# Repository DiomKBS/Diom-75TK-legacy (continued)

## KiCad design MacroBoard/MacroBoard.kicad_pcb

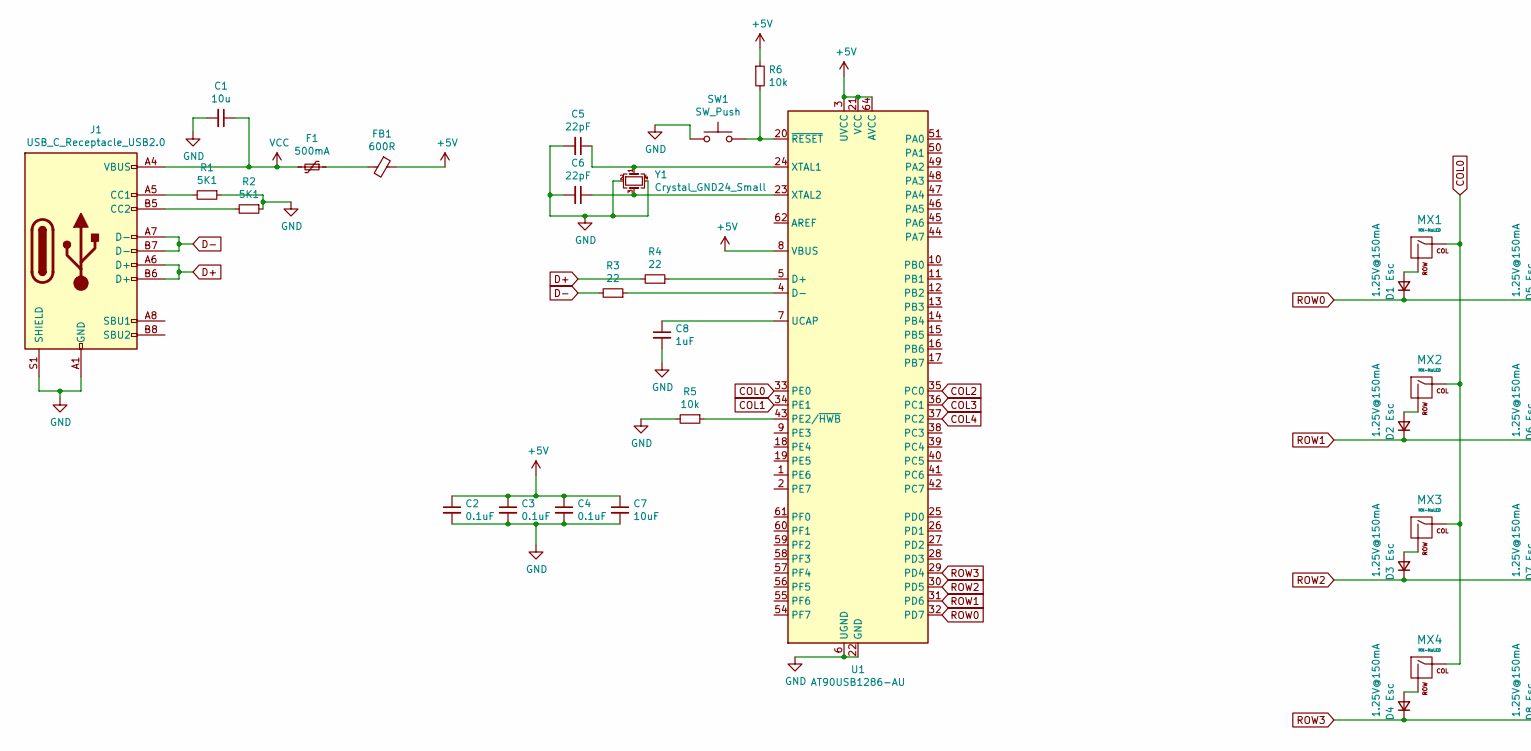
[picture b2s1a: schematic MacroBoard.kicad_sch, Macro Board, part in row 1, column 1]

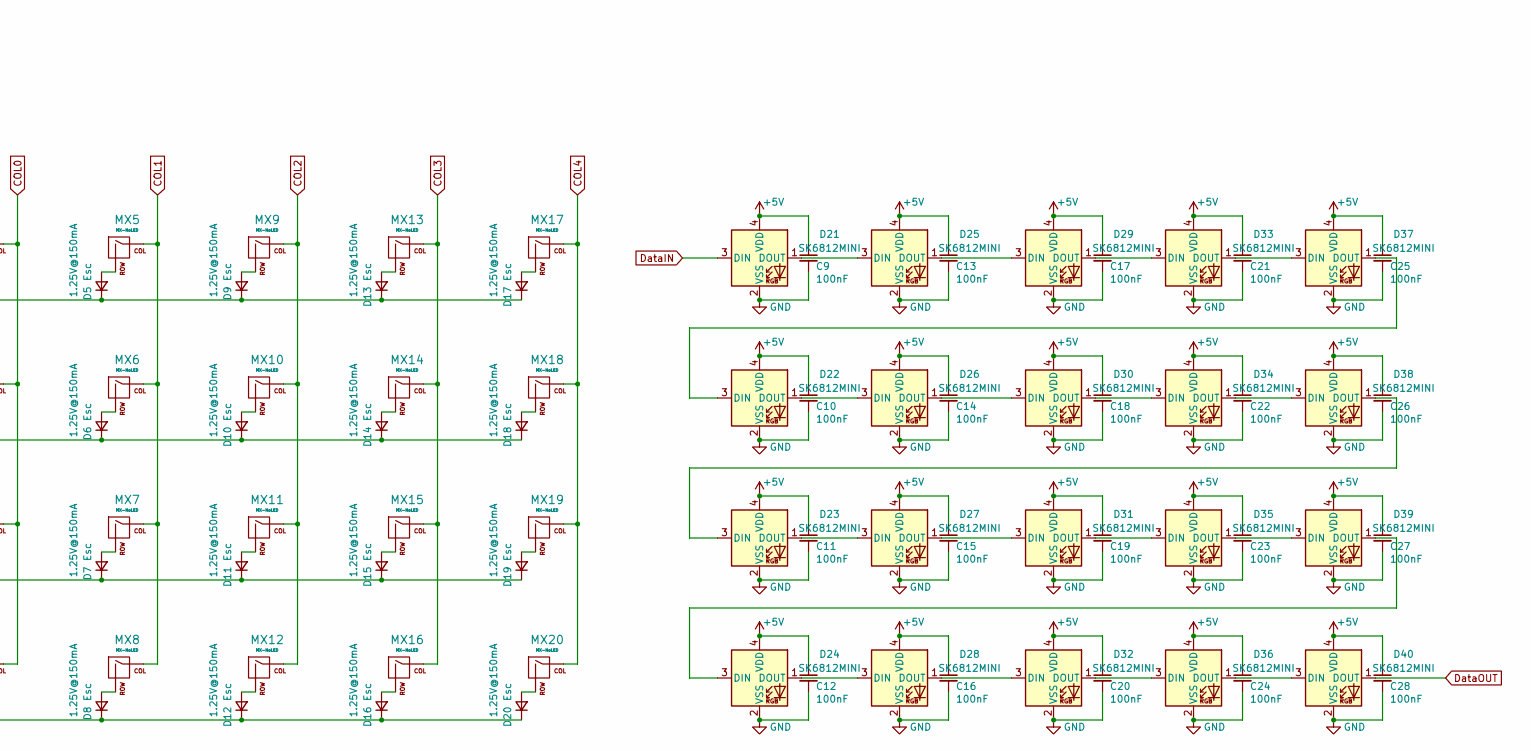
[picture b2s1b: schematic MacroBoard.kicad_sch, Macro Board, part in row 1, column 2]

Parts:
C1: 10u; C_0805_2012Metric
C2, C3, C4: 0.1uF; C_0805_2012Metric
C5, C6: 22pF; C_0805_2012Metric
C7: 10uF; C_0805_2012Metric
C8: 1uF; C_0805_2012Metric
C9, C10, C11, C12, C13, C14, C15, C16, C17, C18, C19, C20, C21, C22, C23, C24, C25, C26, C27, C28: 100nF; led_capacitor
D1, D2, D3, D4, D5, D6, D7, D8, D9, D10, D11, D12, D13, D14, D15, D16, D17, D18, D19, D20: 1.25V@150mA; D_SOD-123
D21, D22, D23, D24, D25, D26, D27, D28, D29, D30, D31, D32, D33, D34, D35, D36, D37, D38, D39, D40: SK6812MINI; SK6812MINI_3.5x3.7mm_SMD-Flipped-Back
F1: 500mA; Fuse_1206_3216Metric
FB1: 600R; Ferrite_Bead_0603
J1: USB_C_Receptacle_USB2.0; USB_C_Receptacle_HRO_TYPE-C-31-M-12
MX1, MX2, MX3, MX4, MX5, MX6, MX7, MX8, MX9, MX10, MX11, MX12, MX13, MX14, MX15, MX16, MX17, MX18, MX19, MX20: MX-NoLED; Kailh-Hotswap-1U
R1, R2: 5K1; R_0805_2012Metric
R3, R4: 22; R_0805_2012Metric
R5, R6: 10k; R_0805_2012Metric
SW1: SW_Push; SKQG-1155865
U1: AT90USB1286-AU; TQFP-64_14x14mm_P0.8mm
Y1: Crystal_GND24_Small; Crystal_SMD_3225-4Pin_3.2x2.5mm

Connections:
+5V: C2.1, C3.1, C4.1, C7.1, C9.1, C10.1, C11.1, C12.1, C13.1, C14.1, C15.1, C16.1, C17.1, C18.1, C19.1, C20.1, C21.1, C22.1, C23.1, C24.1, C25.1, C26.1, C27.1, C28.1, D21.4 (VDD), D22.4 (VDD), D23.4 (VDD), D24.4 (VDD), D25.4 (VDD), D26.4 (VDD), D27.4 (VDD), D28.4 (VDD), D29.4 (VDD), D30.4 (VDD), D31.4 (VDD), D32.4 (VDD), D33.4 (VDD), D34.4 (VDD), D35.4 (VDD), D36.4 (VDD), D37.4 (VDD), D38.4 (VDD), D39.4 (VDD), D40.4 (VDD), FB1.1, R6.1, U1.3 (UVCC), U1.8 (VBUS), U1.21 (VCC), U1.52 (VCC), U1.64 (AVCC)
COL0: MX1.1 (COL), MX2.1 (COL), MX3.1 (COL), MX4.1 (COL), U1.33 (PE0)
COL1: MX5.1 (COL), MX6.1 (COL), MX7.1 (COL), MX8.1 (COL), U1.34 (PE1)
COL2: MX9.1 (COL), MX10.1 (COL), MX11.1 (COL), MX12.1 (COL), U1.35 (PC0)
COL3: MX13.1 (COL), MX14.1 (COL), MX15.1 (COL), MX16.1 (COL), U1.36 (PC1)
COL4: MX17.1 (COL), MX18.1 (COL), MX19.1 (COL), MX20.1 (COL), U1.37 (PC2)
D+: J1.A6 (D+), J1.B6 (D+), R4.2
D-: J1.A7 (D-), J1.B7 (D-), R3.2
DataIN: D21.3 (DIN)
DataOUT: D40.1 (DOUT)
GND: C1.2, C2.2, C3.2, C4.2, C5.2, C6.2, C7.2, C8.2, C9.2, C10.2, C11.2, C12.2, C13.2, C14.2, C15.2, C16.2, C17.2, C18.2, C19.2, C20.2, C21.2, C22.2, C23.2, C24.2, C25.2, C26.2, C27.2, C28.2, D21.2 (VSS), D22.2 (VSS), D23.2 (VSS), D24.2 (VSS), D25.2 (VSS), D26.2 (VSS), D27.2 (VSS), D28.2 (VSS), D29.2 (VSS), D30.2 (VSS), D31.2 (VSS), D32.2 (VSS), D33.2 (VSS), D34.2 (VSS), D35.2 (VSS), D36.2 (VSS), D37.2 (VSS), D38.2 (VSS), D39.2 (VSS), D40.2 (VSS), J1.A1 (GND), J1.A12 (GND), J1.B1 (GND), J1.B12 (GND), J1.S1 (SHIELD), R1.1, R2.1, R5.2, SW1.1, U1.6 (UGND), U1.22 (GND), U1.53 (GND), U1.63 (GND), Y1.2, Y1.4
unnamed: C5.1, U1.24 (XTAL1), Y1.1
unnamed: C6.1, U1.23 (XTAL2), Y1.3
unnamed: C8.1, U1.7 (UCAP)
unnamed: D1.2 (A), MX1.2 (ROW)
unnamed: D2.2 (A), MX2.2 (ROW)
unnamed: D3.2 (A), MX3.2 (ROW)
unnamed: D4.2 (A), MX4.2 (ROW)
unnamed: D5.2 (A), MX5.2 (ROW)
unnamed: D6.2 (A), MX6.2 (ROW)
unnamed: D7.2 (A), MX7.2 (ROW)
unnamed: D8.2 (A), MX8.2 (ROW)
unnamed: D9.2 (A), MX9.2 (ROW)
unnamed: D10.2 (A), MX10.2 (ROW)
unnamed: D11.2 (A), MX11.2 (ROW)
unnamed: D12.2 (A), MX12.2 (ROW)
unnamed: D13.2 (A), MX13.2 (ROW)
unnamed: D14.2 (A), MX14.2 (ROW)
unnamed: D15.2 (A), MX15.2 (ROW)
unnamed: D16.2 (A), MX16.2 (ROW)
unnamed: D17.2 (A), MX17.2 (ROW)
unnamed: D18.2 (A), MX18.2 (ROW)
unnamed: D19.2 (A), MX19.2 (ROW)
unnamed: D20.2 (A), MX20.2 (ROW)
unnamed: D21.1 (DOUT), D25.3 (DIN)
unnamed: D22.1 (DOUT), D26.3 (DIN)
unnamed: D22.3 (DIN), D37.1 (DOUT)
unnamed: D23.1 (DOUT), D27.3 (DIN)
unnamed: D23.3 (DIN), D38.1 (DOUT)
unnamed: D24.1 (DOUT), D28.3 (DIN)
unnamed: D24.3 (DIN), D39.1 (DOUT)
unnamed: D25.1 (DOUT), D29.3 (DIN)
unnamed: D26.1 (DOUT), D30.3 (DIN)
unnamed: D27.1 (DOUT), D31.3 (DIN)
unnamed: D28.1 (DOUT), D32.3 (DIN)
unnamed: D29.1 (DOUT), D33.3 (DIN)
unnamed: D30.1 (DOUT), D34.3 (DIN)
unnamed: D31.1 (DOUT), D35.3 (DIN)
unnamed: D32.1 (DOUT), D36.3 (DIN)
unnamed: D33.1 (DOUT), D37.3 (DIN)
unnamed: D34.1 (DOUT), D38.3 (DIN)
unnamed: D35.1 (DOUT), D39.3 (DIN)
unnamed: D36.1 (DOUT), D40.3 (DIN)
unnamed: F1.1, FB1.2
unnamed: J1.A5 (CC1), R1.2
unnamed: J1.B5 (CC2), R2.2
unnamed: R3.1, U1.4 (D-)
unnamed: R4.1, U1.5 (D+)
unnamed: R5.1, U1.43 (PE2/~HWB)
unnamed: R6.2, SW1.2, U1.20 (~RESET)
ROW0: D1.1 (K), D5.1 (K), D9.1 (K), D13.1 (K), D17.1 (K), U1.32 (PD7)
ROW1: D2.1 (K), D6.1 (K), D10.1 (K), D14.1 (K), D18.1 (K), U1.31 (PD6)
ROW2: D3.1 (K), D7.1 (K), D11.1 (K), D15.1 (K), D19.1 (K), U1.30 (PD5)
ROW3: D4.1 (K), D8.1 (K), D12.1 (K), D16.1 (K), D20.1 (K), U1.29 (PD4)
VCC: C1.1, F1.2, J1.A4 (VBUS), J1.A9 (VBUS), J1.B4 (VBUS), J1.B9 (VBUS)

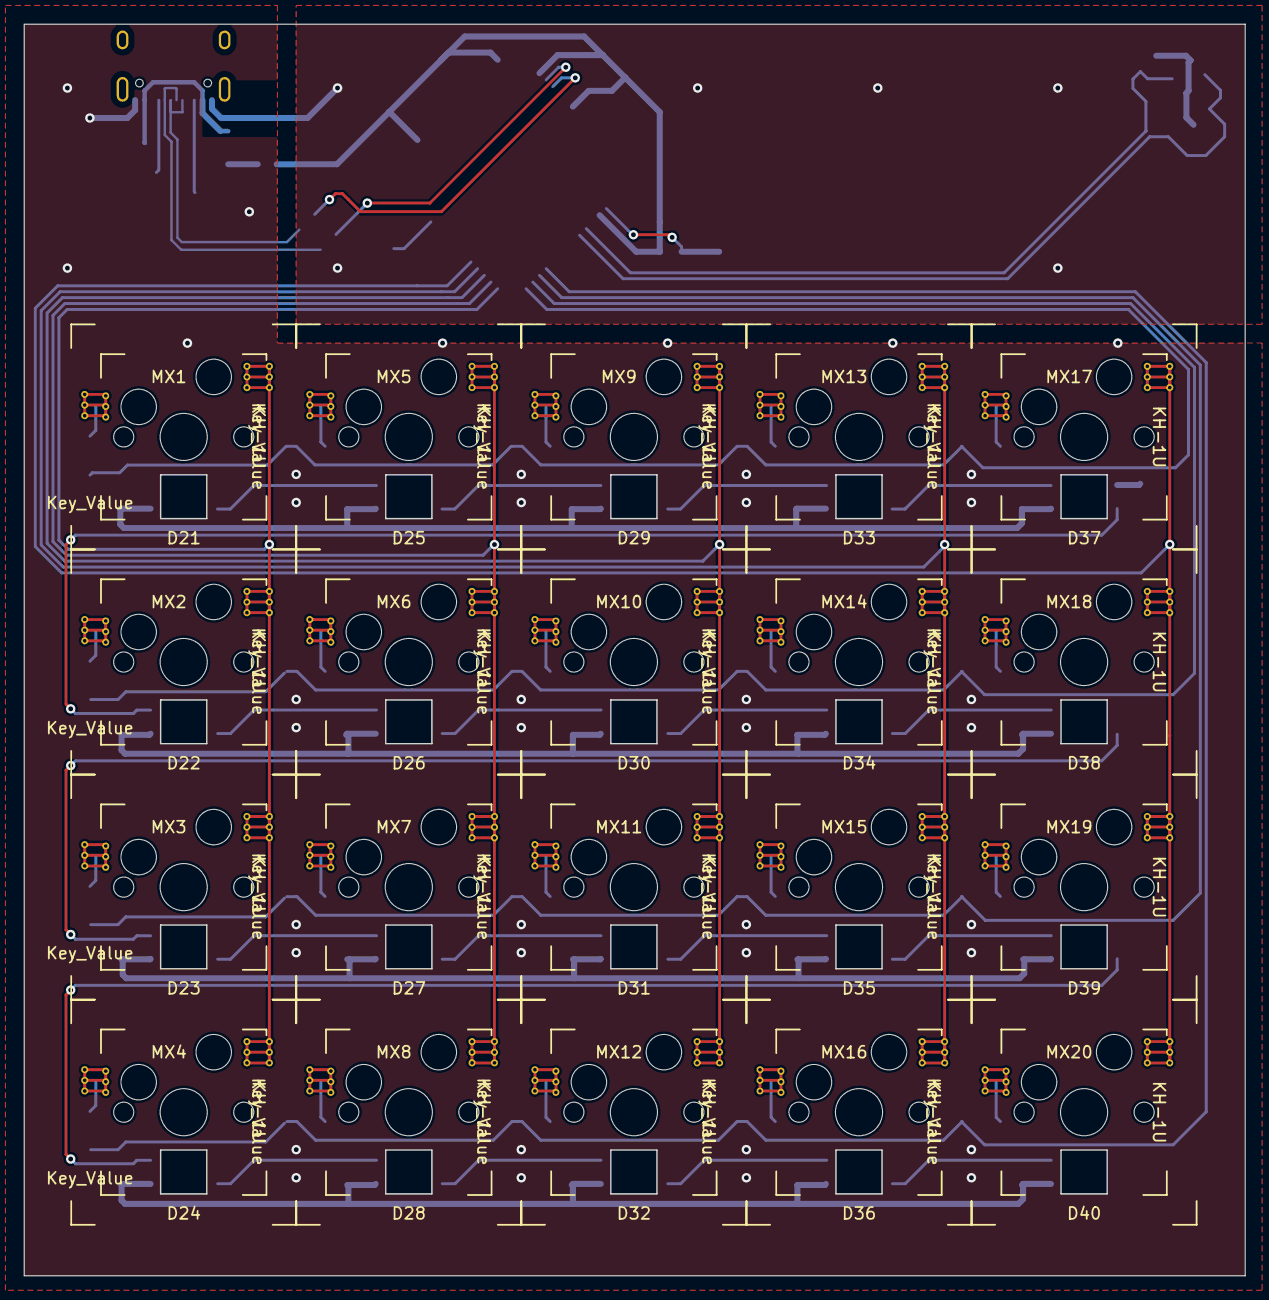
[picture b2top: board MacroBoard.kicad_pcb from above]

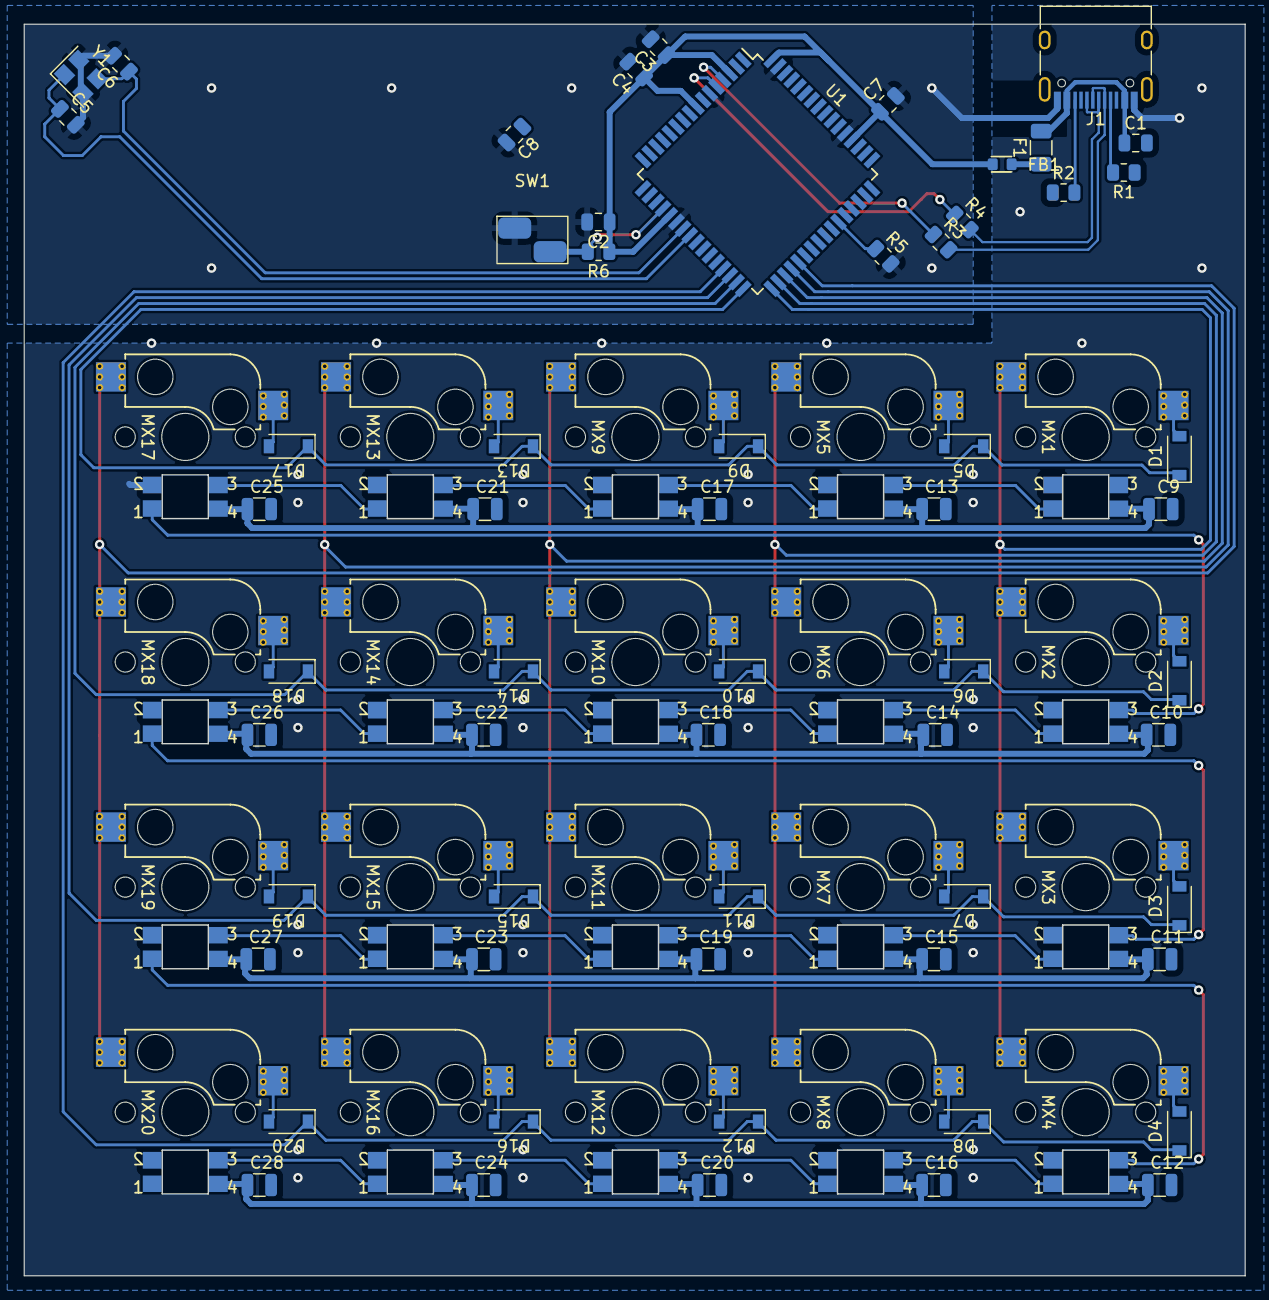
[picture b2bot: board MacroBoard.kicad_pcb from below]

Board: 2 copper layers, 103.3 x 105.9 mm, 100 parts (60 on the bottom side), 63 nets.

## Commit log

2022-02-14 Added KiCad Project
2022-02-21 Logo
2022-03-05 Added Submodules
2022-03-05 Added Libraries to Project
2022-03-06 Logo now better
2022-03-06 Updated Layout
2022-03-06 Finished MCU
2022-03-06 USB Circuit added
2022-03-06 Finished Matrix
2022-03-06 Renamed Switches
2022-03-06 Added Footprints
2022-04-14 Changed Switches to have no LED
    +Wired left arrow
2022-04-14 KiCat6
2022-04-14 Added LEDs to the Schematic
2022-04-14 Submodule, LEDs, Footprints
2022-04-14 Changed Submodules
2022-04-14 Started PCB + Changed Footprints
2022-04-15 Philipp Spacebar
2022-04-15 Added Enter (Commit Tests)
2022-04-15 start of leds
2022-04-15 update sub
2022-04-15 Finished Switch Layout
2022-04-15 Diode placement, Alternative Bottom Rows
    -New Footprints
2022-04-15 Changed Footprint for Ferrite
2022-04-15 Placed all LEDs
2022-04-16 PCB Size, LED Footprints
2022-04-16 Updated Submodule
2022-04-17 coper plates backup Philipp
2022-04-17 Copper Plates Backup (Simon)
2022-04-17 MCU start
2022-04-17 Wired Rows and Columns
2022-04-17 Revert "Merge branch 'main' of https://github.com/DiomKBS/Diom-75TK"
    This reverts commit d4d5be1e366361c8f7f1bcceadc728d9bff743c0, reversing
    changes made to cc8c22ed399807c67032a22d6e05ce12f162b48f.
2022-04-17 5V and usb
2022-04-17 Rounded PCB Edges
2022-04-17 LED Shenanigans
2022-04-17 LED Data Buses finished
2022-04-17 Added LED Net
2022-04-18 led go brrrr
2022-04-19 MCU finished
2022-04-19 change diod
2022-04-19 update submodule
2022-04-19 change Crystal
2022-04-19 Added missing Column
2022-04-19 Added missing LED Ground
2022-04-19 gerber and cahnge value of diodes
2022-04-19 change footprint
2022-04-19 Backplate Stuff
2022-04-20 add tree graphic
2022-04-20 tree
2022-04-20 switchj
2022-04-20 Revert "idk"
    This reverts commit e0f5a71326574bffc903f545a908fb671bec7abd.
2022-04-20 Revert "update"
    This reverts commit cd09d255f93104ab093fe68beff66254dddae383.
2022-04-20 Revert "switchj"
    This reverts commit d5a96ddcb071ce4a4afd099785118bfee5e594ee.
2022-04-20 Reset Switch updated
2022-04-21 Rough Col and Row wiring
2022-04-21 some silk
2022-04-21 Via for Col and Row
2022-04-21 Via updated
2022-04-21 All Rows and Columns connected
2022-04-21 LED Data Bus connected
2022-04-21 Reset Switch Footprint Updated
2022-04-21 Silkscreen Legends updated
2022-04-21 Probably Finished
2022-04-21 Small Changes
2022-04-21 New Diode Placement and Cols and Rows
2022-04-21 macro board
2022-04-21 fix merge 2
2022-04-22 makro board
2022-04-22 Seperate Sheets, Diode Data, Cols + Rows Finished
2022-04-22 Ground Planes, USB Wiring, MCU Wiring
2022-04-22 LED Diode Placement finished
2022-04-23 macro teardrop and roundet tracks
2022-04-24 LED +5 Wired, COL and ROW Buses nearly finished
2022-04-24 Roughly finished, Rotary Encoder in Prev
2022-04-24 +5V for LED Connected
2022-04-24 Fixed all Errors
    Only 1009 Warnings remain :D
2022-04-24 Fixed some Warnings
2022-04-24 3D Models
2022-04-24 Added Diom Lettering
2022-04-24 Updated Lettering
2022-04-25 roundet tracks
2022-04-27 Optical Track changes
2022-04-27 Mostly optical Changes
2022-04-27 New Connector
2022-04-27 usb c
2022-04-27 Optimized PCB for rounded Tracks
    Also new PCB with rounded Tracks (no errors)
2022-04-30 Now only 2 alternative bottom rows
    6.25U (Three 1U Keys to the right) and 7U (One 1.25U Key and one 1U Key to the right) Space Supported
    Also new rounded PCB
2022-05-03 New Logos
2022-05-04 New .svg's
2022-05-04 Changes to .svg's
2022-05-11 datalines and mosfet
2022-05-11 Relocated JST Connector
2022-05-12 change port position
2022-05-15 Added Plate Gaskets
    Diom Logo on Plate
2022-05-15 Updated Submodules
2022-05-15 Gerber Files
2022-05-16 changes:\n\n -change zones\n -add mounting holes\n -change via size
2022-05-22 production and CAD preparations
2022-05-24 Copper Frame on Backplate
2022-05-24 New Gerber for Backplate
2022-05-24 removed submodule Switches
2022-05-24 removed submodule josh
2022-05-24 add josh
2022-05-24 LFS for zip
2022-05-24 add Render Files
2022-06-19 production?
    still hope
2022-06-27 final gerber generation
2022-09-13 Fixed LEDs
2022-11-05 New Gerbers, New Rounded
